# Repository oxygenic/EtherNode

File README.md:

# EtherNode
Slim STM32H7-based Ethernet device with several IOs and signal types which can be controlled via Telnet, supports MODBUS, REST and MQTT as well as small programs running from the device directly 

The EtherNode is an industrial IO-extender that comes with different types of input- and output-signals and a wide range of communication interfaces. Thus it can be used as remote Ethernet IO-module for different other scenarios and applications. Possible usage scenarios would be applications where the EtherNode acts as slim TCP module for a PLC and where it autonomously performs distributed and remote I/O operations that are triggered via simple and easy to use commands.

The EtherNode Compact IO module can be integrated into every machine network and provides the following features:
- wide-range power supply allows input voltages from 9V to 32V
- 8 galvanically insulated digital inputs which can be operated with external power in range 5..24V
- 2 of the digital inputs optionally can be used with a quadrature encoder for counting steps (position), speed and acceleration
- 8 galvanically insulated digital outputs which can be operated with external power in range 5..24V
- 2 of the digital outputs optionally can issue freely definable frequencies of up to 500 kHz with programmable pulse-width (PWM)
- 2 of the digital outputs optionally can be used to drive control two stepper motor axes with a step frequency of up to 100 kHz, acceleration ramps and referencing
- 2 high-impedance analogue inputs in range 0..10V with a resolution of 16 bits
- Ethernet interface to connect with host (control-PC / embedded device / PLC)
- control via Telnet ASCII commands, MODBUS, MQTT (plain and JSON) or HTTP REST API (plain and JSON)
- stand-alone operation: conditions and flows can be defined and stored on the device for autonomous operation wiht and without communication via the communication interfaces
- fully operational with any control device such as a PLC or even a plain PC or a Raspberry Pi
- board designed to fit into compact housing with DIN rail mounting clamp available at https://de.rs-online.com/web/p/din-schienen-gehause/1862290 and at https://de.rs-online.com/web/p/din-schienen-gehause/0336868

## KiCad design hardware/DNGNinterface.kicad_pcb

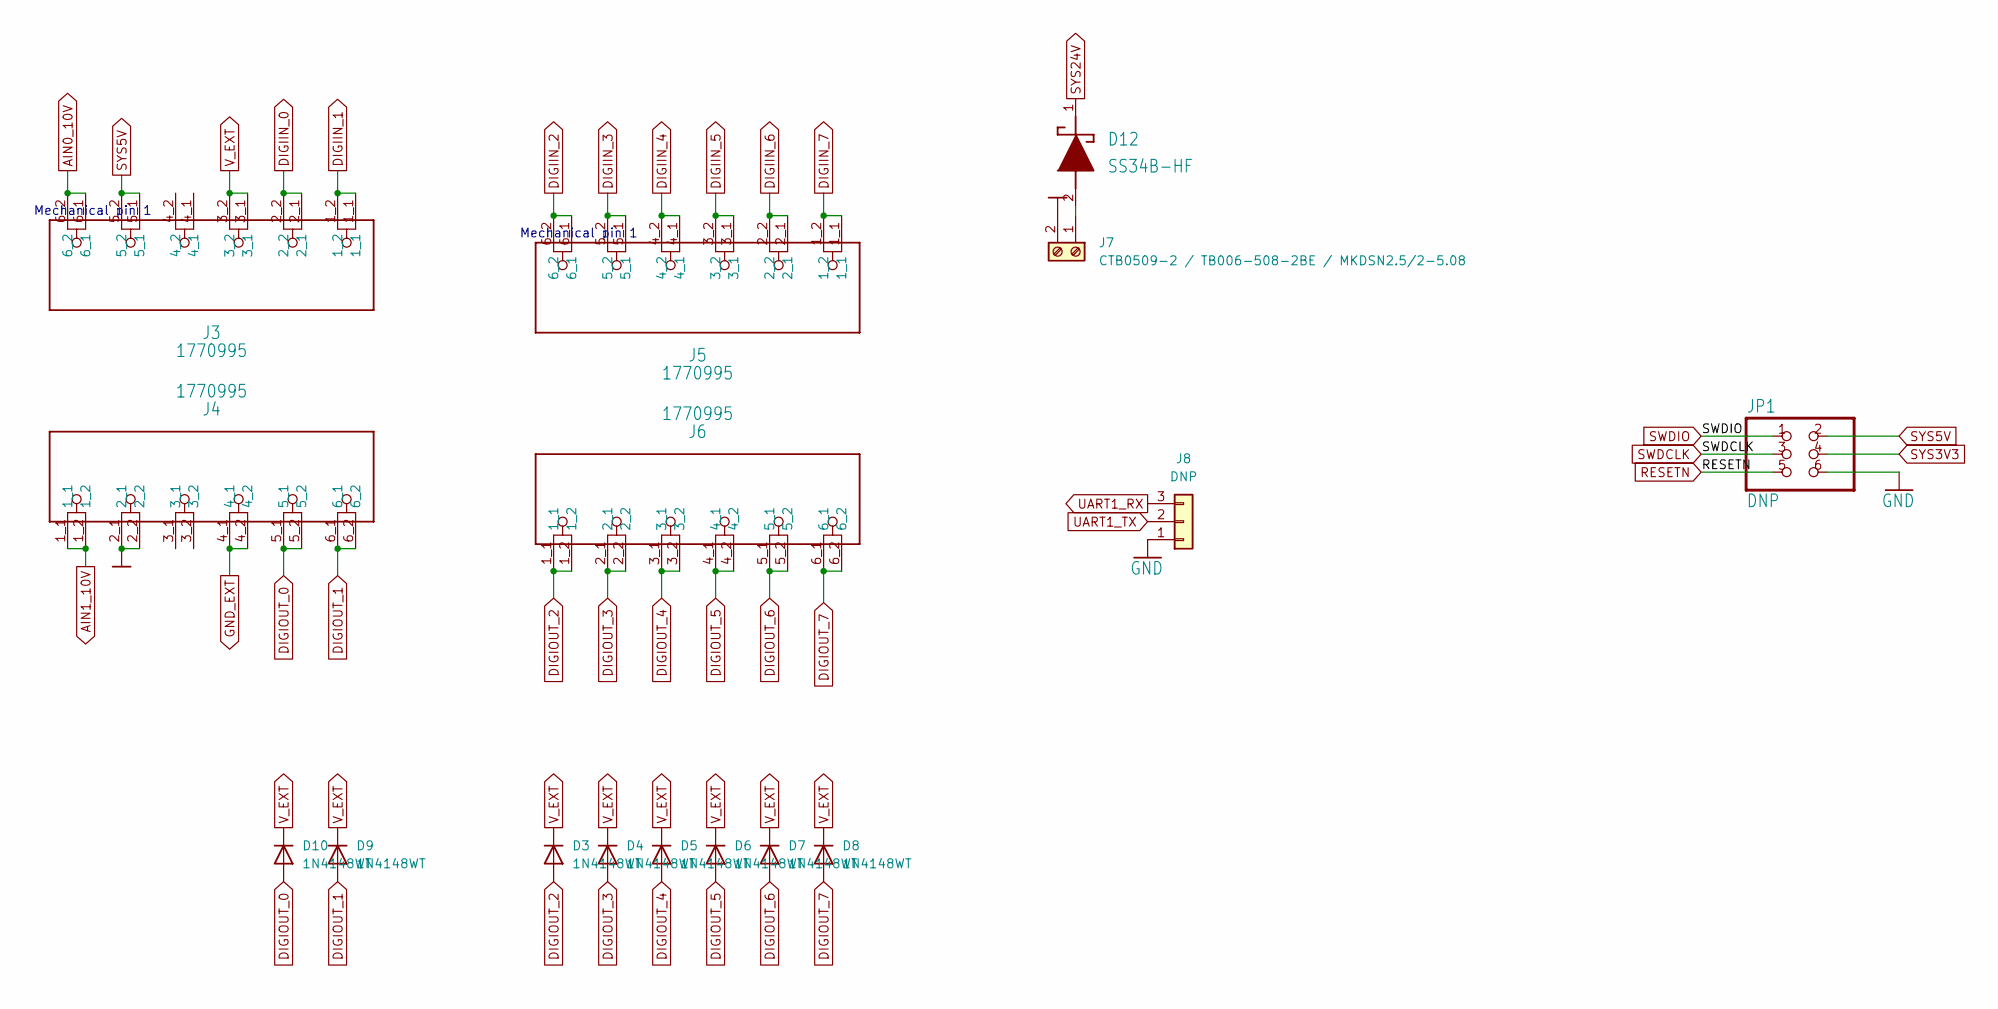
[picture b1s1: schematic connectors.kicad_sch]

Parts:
D3, D4, D5, D6, D7, D8, D9, D10: 1N4148WT; D_SOD-523
D12: SS34B-HF; SS34
J3, J4, J5, J6: 1770995; PHOENIX_1770995
J7: CTB0509-2 / TB006-508-2BE / MKDSN2.5/2-5.08; TerminalBlock_Phoenix_MKDS-1,5-2-5.08_1x02_P5.08mm_Horizont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
J8: DNP; PinHeader_1x03_P2.54mm_Vertical
JP1: DNP; PinHeader_2x03_P2.54mm_Vertical

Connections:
AIN0_10V: J3.6_1, J3.6_2; also elsewhere on the board
AIN1_10V: J4.1_1, J4.1_2; also elsewhere on the board
DIGIIN_0: J3.2_1, J3.2_2; also elsewhere on the board
DIGIIN_1: J3.1_1, J3.1_2; also elsewhere on the board
DIGIIN_2: J5.6_1, J5.6_2; also elsewhere on the board
DIGIIN_3: J5.5_1, J5.5_2; also elsewhere on the board
DIGIIN_4: J5.4_1, J5.4_2; also elsewhere on the board
DIGIIN_5: J5.3_1, J5.3_2; also elsewhere on the board
DIGIIN_6: J5.2_1, J5.2_2; also elsewhere on the board
DIGIIN_7: J5.1_1, J5.1_2; also elsewhere on the board
DIGIOUT_0: D10.2 (A), J4.5_1, J4.5_2; also elsewhere on the board
DIGIOUT_1: D9.2 (A), J4.6_1, J4.6_2; also elsewhere on the board
DIGIOUT_2: D3.2 (A), J6.1_1, J6.1_2; also elsewhere on the board
DIGIOUT_3: D4.2 (A), J6.2_1, J6.2_2; also elsewhere on the board
DIGIOUT_4: D5.2 (A), J6.3_1, J6.3_2; also elsewhere on the board
DIGIOUT_5: D6.2 (A), J6.4_1, J6.4_2; also elsewhere on the board
DIGIOUT_6: D7.2 (A), J6.5_1, J6.5_2; also elsewhere on the board
DIGIOUT_7: D8.2 (A), J6.6_1, J6.6_2; also elsewhere on the board
GND: J4.2_1, J4.2_2, J7.2, J8.1, JP1.6; also elsewhere on the board
GND_EXT: J4.4_1, J4.4_2; also elsewhere on the board
unnamed: D12.2 (A), J7.1
RESETN: JP1.5; also elsewhere on the board
SWDCLK: JP1.3; also elsewhere on the board
SWDIO: JP1.1; also elsewhere on the board
SYS3V3: JP1.4; also elsewhere on the board
SYS5V: J3.5_1, J3.5_2, JP1.2; also elsewhere on the board
SYS24V: D12.1 (K); also elsewhere on the board
UART1_RX: J8.3; also elsewhere on the board
UART1_TX: J8.2; also elsewhere on the board
V_EXT: D3.1 (K), D4.1 (K), D5.1 (K), D6.1 (K), D7.1 (K), D8.1 (K), D9.1 (K), D10.1 (K), J3.3_1, J3.3_2; also elsewhere on the board

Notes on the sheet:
Mechanical pin 1

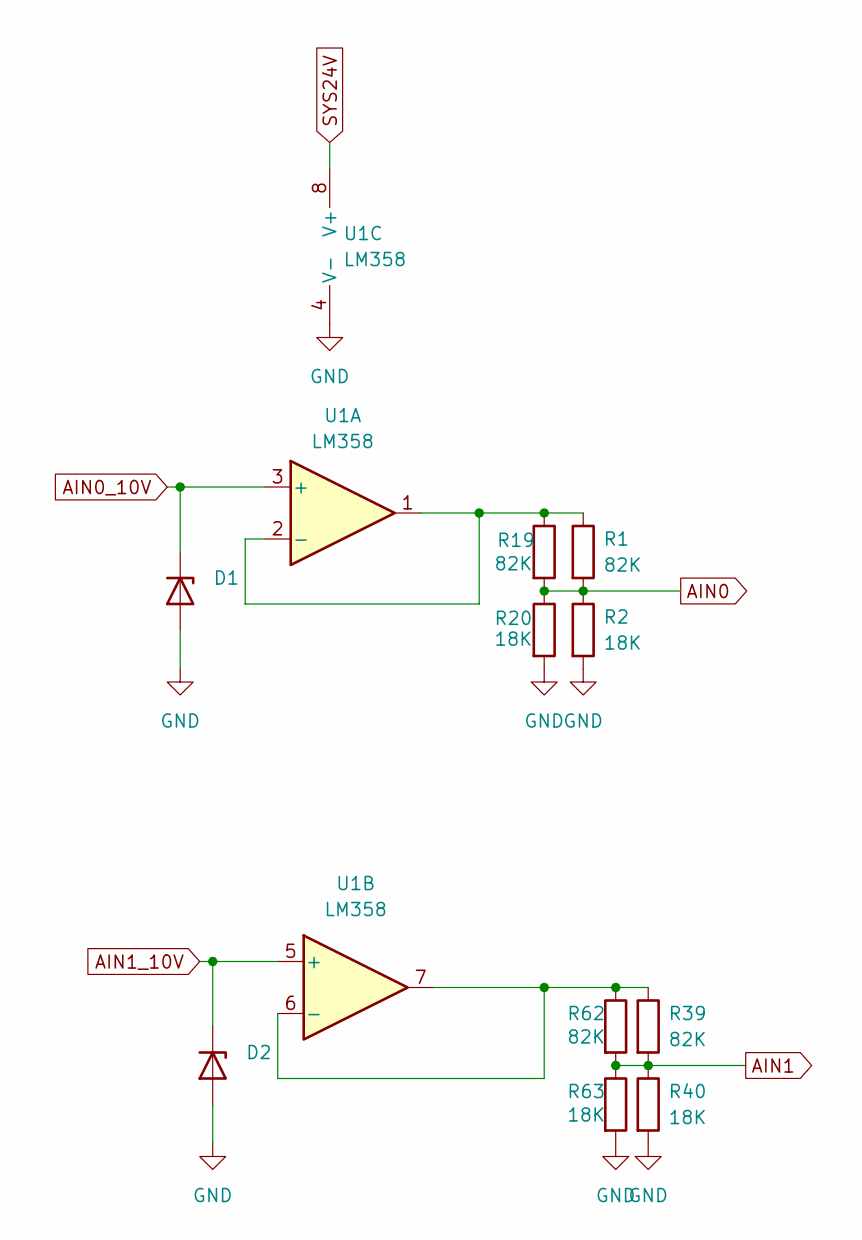
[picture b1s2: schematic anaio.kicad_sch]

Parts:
D1, D2: BZX84B10 / BZX84C10; SOT-23
R1, R19, R39, R62: 82K; R_0603_1608Metric
R2, R20, R40, R63: 18K; R_0603_1608Metric
U1: LM358; LM358DT

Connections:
AIN0: R1.2, R2.1, R19.2, R20.1; also elsewhere on the board
AIN0_10V: D1.3 (K), U1.3 (+); also elsewhere on the board
AIN1: R39.2, R40.1, R62.2, R63.1; also elsewhere on the board
AIN1_10V: D2.3 (K), U1.5 (+); also elsewhere on the board
GND: D1.1 (A), D2.1 (A), R2.2, R20.2, R40.2, R63.2, U1.4 (V-); also elsewhere on the board
unnamed: R1.1, R19.1, U1.1, U1.2 (-)
unnamed: R39.1, R62.1, U1.6 (-), U1.7
SYS24V: U1.8 (V+); also elsewhere on the board

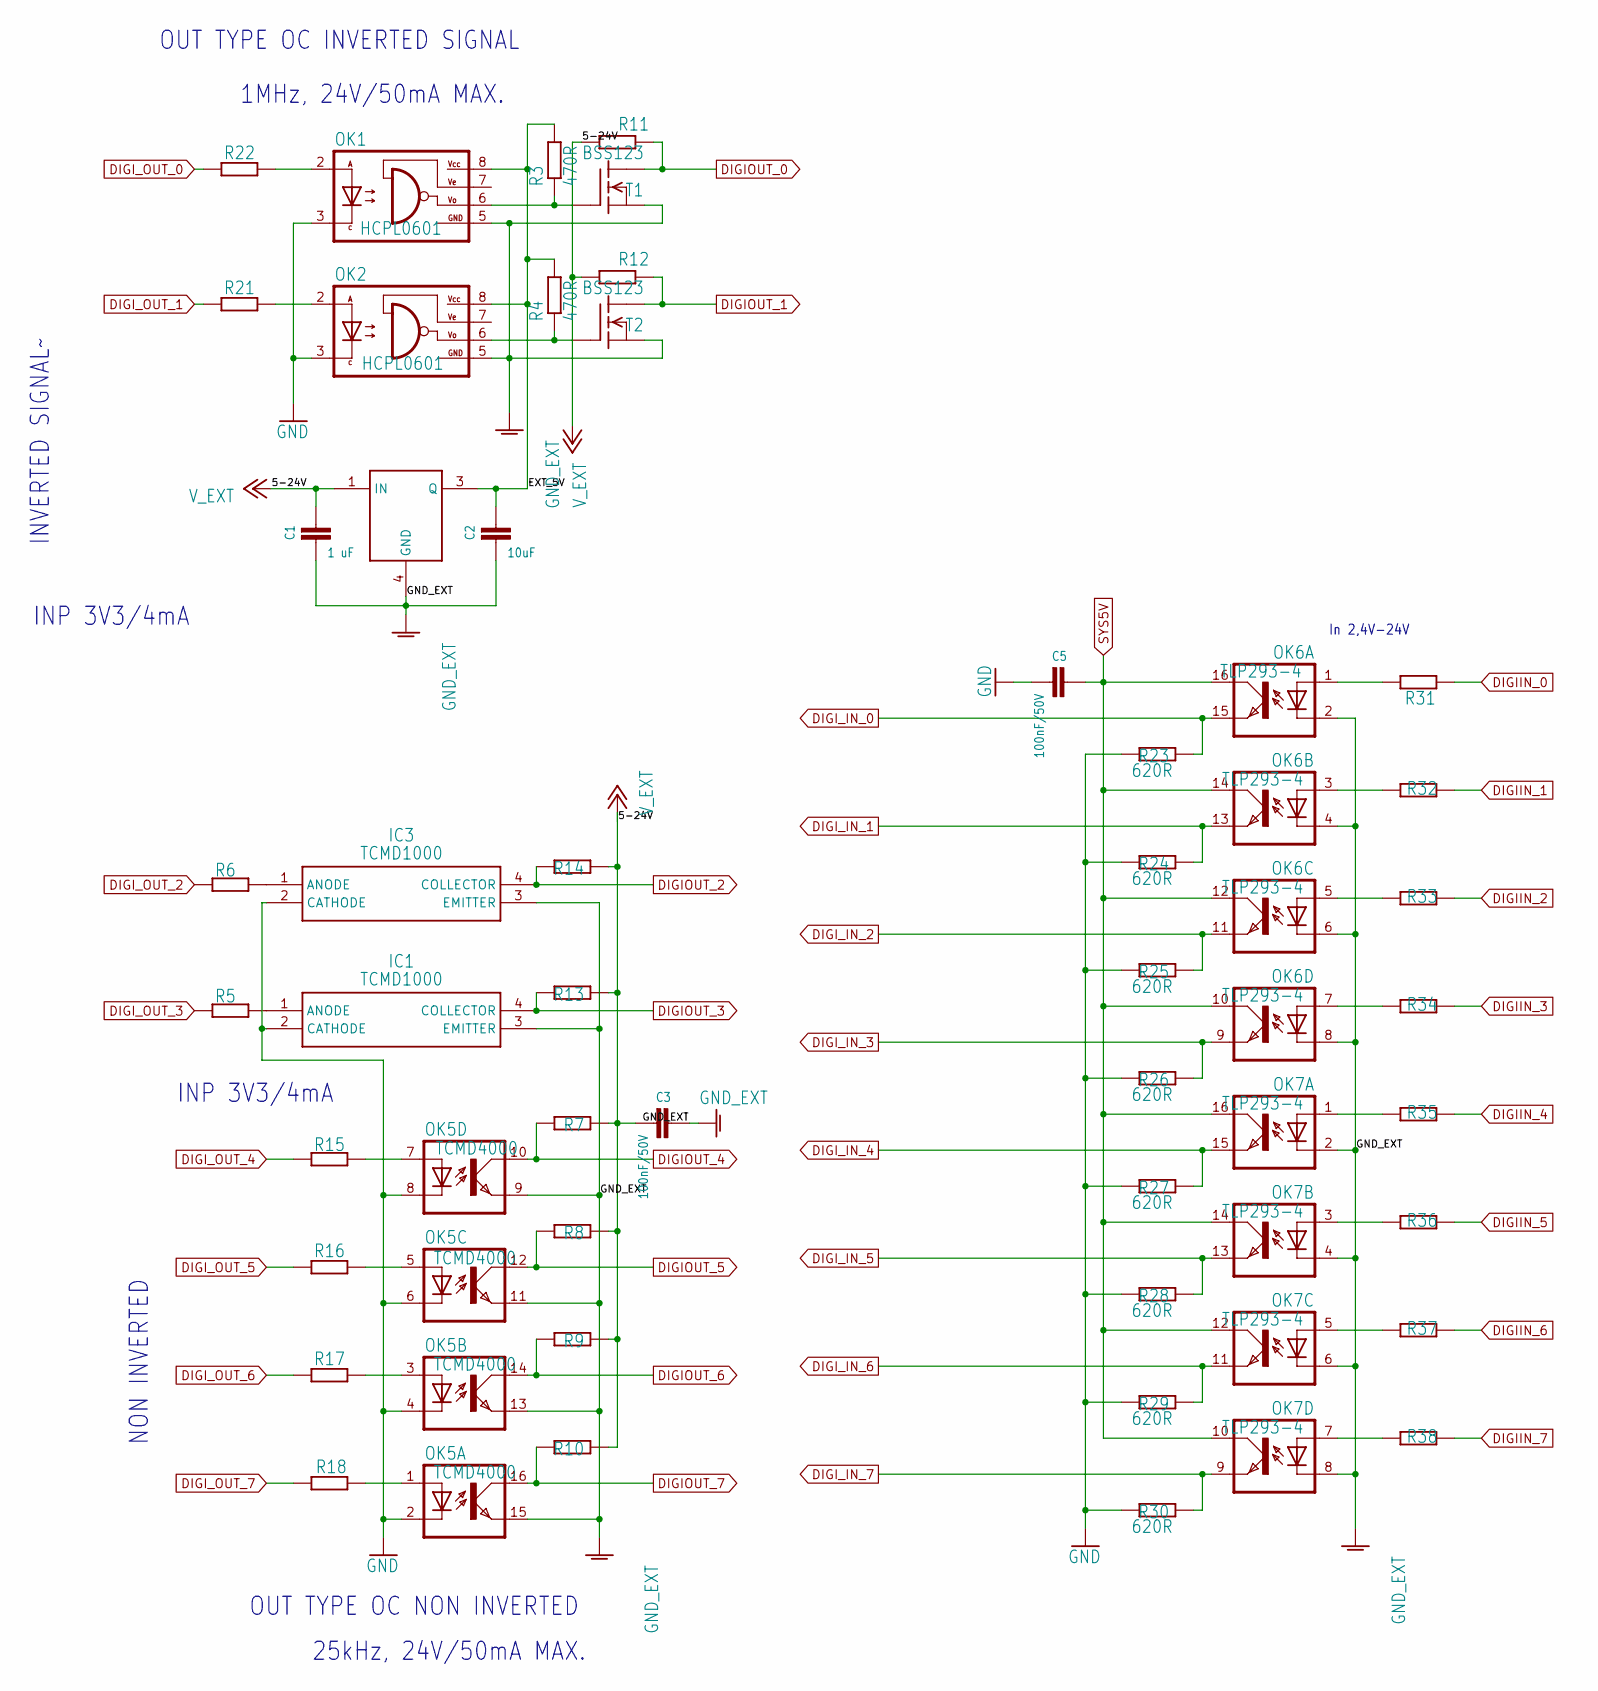
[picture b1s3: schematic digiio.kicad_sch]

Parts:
C1: 1 uF; C_0603_1608Metric
C2: 10uF; C_0603_1608Metric
C3, C5: 100nF/50V; C_0603_1608Metric
IC1, IC3: TCMD1000; SOIC127P695X210-4N
OK1, OK2: HCPL0601; HCLP0601
OK5: TCMD4000
OK6, OK7: TLP293-4; TLP293-4(E
R3, R4: 470R; R_0603_1608Metric
R5, R6, R15, R16, R17, R18, R21, R22: 270 R; R_0603_1608Metric
R7, R8, R9, R10, R11, R12, R13, R14: 2k2 0,75W ASC2010-2K2FT4 / RMCF2010JT2K20; R_2010_5025Metric
R23, R24, R25, R26, R27, R28, R29, R30: 620R; R_0603_1608Metric
R31, R32, R33, R34, R35, R36, R37, R38: 1k 0,75W RC2010JK-071KL / RMCF2010JT1K00 / CRMA20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; R_2010_5025Metric
T1, T2: BSS123
U$1: NCV4274CDT50RKG / NCV4274ADT50 / BD50FC0FP; NCV4274CDT50RKG

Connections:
/DigiIO/EXT_5V: C2.1, OK1.8 (VCC), OK2.8 (VCC), R3.2, R4.2, U$1.3 (Q)
DIGIIN_0: R31.2; also elsewhere on the board
DIGIIN_1: R32.2; also elsewhere on the board
DIGIIN_2: R33.2; also elsewhere on the board
DIGIIN_3: R34.2; also elsewhere on the board
DIGIIN_4: R35.2; also elsewhere on the board
DIGIIN_5: R36.2; also elsewhere on the board
DIGIIN_6: R37.2; also elsewhere on the board
DIGIIN_7: R38.2; also elsewhere on the board
DIGIOUT_0: R11.2, T1.3 (D1); also elsewhere on the board
DIGIOUT_1: R12.2, T2.3 (D1); also elsewhere on the board
DIGIOUT_2: IC3.4 (COLLECTOR), R14.2; also elsewhere on the board
DIGIOUT_3: IC1.4 (COLLECTOR), R13.2; also elsewhere on the board
DIGIOUT_4: OK5.10 (COL), R7.2; also elsewhere on the board
DIGIOUT_5: OK5.12 (COL), R8.2; also elsewhere on the board
DIGIOUT_6: OK5.14 (COL), R9.2; also elsewhere on the board
DIGIOUT_7: OK5.16 (COL), R10.2; also elsewhere on the board
DIGI_IN_0: OK6.15 (EMIT), R23.1; also elsewhere on the board
DIGI_IN_1: OK6.13 (EMIT), R24.1; also elsewhere on the board
DIGI_IN_2: OK6.11 (EMIT), R25.1; also elsewhere on the board
DIGI_IN_3: OK6.9 (EMIT), R26.1; also elsewhere on the board
DIGI_IN_4: OK7.15 (EMIT), R27.1; also elsewhere on the board
DIGI_IN_5: OK7.13 (EMIT), R28.1; also elsewhere on the board
DIGI_IN_6: OK7.11 (EMIT), R29.1; also elsewhere on the board
DIGI_IN_7: OK7.9 (EMIT), R30.1; also elsewhere on the board
DIGI_OUT_0: R22.1; also elsewhere on the board
DIGI_OUT_1: R21.1; also elsewhere on the board
DIGI_OUT_2: R6.1; also elsewhere on the board
DIGI_OUT_3: R5.1; also elsewhere on the board
DIGI_OUT_4: R15.1; also elsewhere on the board
DIGI_OUT_5: R16.1; also elsewhere on the board
DIGI_OUT_6: R17.1; also elsewhere on the board
DIGI_OUT_7: R18.1; also elsewhere on the board
GND: C5.2, IC1.2 (CATHODE), IC3.2 (CATHODE), OK1.3 (C), OK2.3 (C), OK5.2 (C), OK5.4 (C), OK5.6 (C), OK5.8 (C), R23.2, R24.2, R25.2, R26.2, R27.2, R28.2, R29.2, R30.2; also elsewhere on the board
GND_EXT: C1.2, C2.2, C3.1, IC1.3 (EMITTER), IC3.3 (EMITTER), OK1.5 (GND), OK2.5 (GND), OK5.9 (EMIT), OK5.11 (EMIT), OK5.13 (EMIT), OK5.15 (EMIT), OK6.2 (C), OK6.4 (C), OK6.6 (C), OK6.8 (C), OK7.2 (C), OK7.4 (C), OK7.6 (C), OK7.8 (C), T1.2 (S), T2.2 (S), U$1.4 (GND); also elsewhere on the board
unnamed: IC1.1 (ANODE), R5.2
unnamed: IC3.1 (ANODE), R6.2
unnamed: OK1.2 (A), R22.2
unnamed: OK1.6 (VO), R3.1, T1.1 (G)
unnamed: OK2.2 (A), R21.2
unnamed: OK2.6 (VO), R4.1, T2.1 (G)
unnamed: OK5.1 (A), R18.2
unnamed: OK5.3 (A), R17.2
unnamed: OK5.5 (A), R16.2
unnamed: OK5.7 (A), R15.2
unnamed: OK6.1 (A), R31.1
unnamed: OK6.3 (A), R32.1
unnamed: OK6.5 (A), R33.1
unnamed: OK6.7 (A), R34.1
unnamed: OK7.1 (A), R35.1
unnamed: OK7.3 (A), R36.1
unnamed: OK7.5 (A), R37.1
unnamed: OK7.7 (A), R38.1
SYS5V: C5.1, OK6.10 (COL), OK6.12 (COL), OK6.14 (COL), OK6.16 (COL), OK7.10 (COL), OK7.12 (COL), OK7.14 (COL), OK7.16 (COL); also elsewhere on the board
V_EXT: C1.1, C3.2, R7.1, R8.1, R9.1, R10.1, R11.1, R12.1, R13.1, R14.1, U$1.1 (IN); also elsewhere on the board

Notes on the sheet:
OUT TYPE OC NON INVERTED
NON INVERTED
INP 3V3/4mA
OUT TYPE OC INVERTED SIGNAL
25kHz, 24V/50mA MAX.
In 2,4V-24V
1MHz, 24V/50mA MAX.
INVERTED SIGNAL~~{}

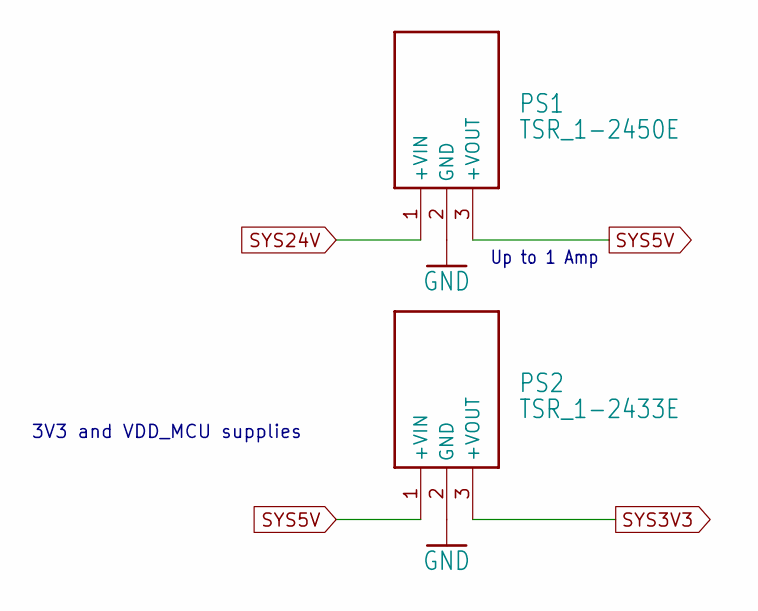
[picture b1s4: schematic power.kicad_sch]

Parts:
PS1: TSR_1-2450E; Converter_DCDC_TRACO_TSR1-xxxxE_THT
PS2: TSR_1-2433E; Converter_DCDC_TRACO_TSR1-xxxxE_THT

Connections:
GND: PS1.2 (GND), PS2.2 (GND); also elsewhere on the board
SYS3V3: PS2.3 (+VOUT); also elsewhere on the board
SYS5V: PS1.3 (+VOUT), PS2.1 (+VIN); also elsewhere on the board
SYS24V: PS1.1 (+VIN); also elsewhere on the board

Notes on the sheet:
Up to 1 Amp
3V3 and VDD_MCU supplies

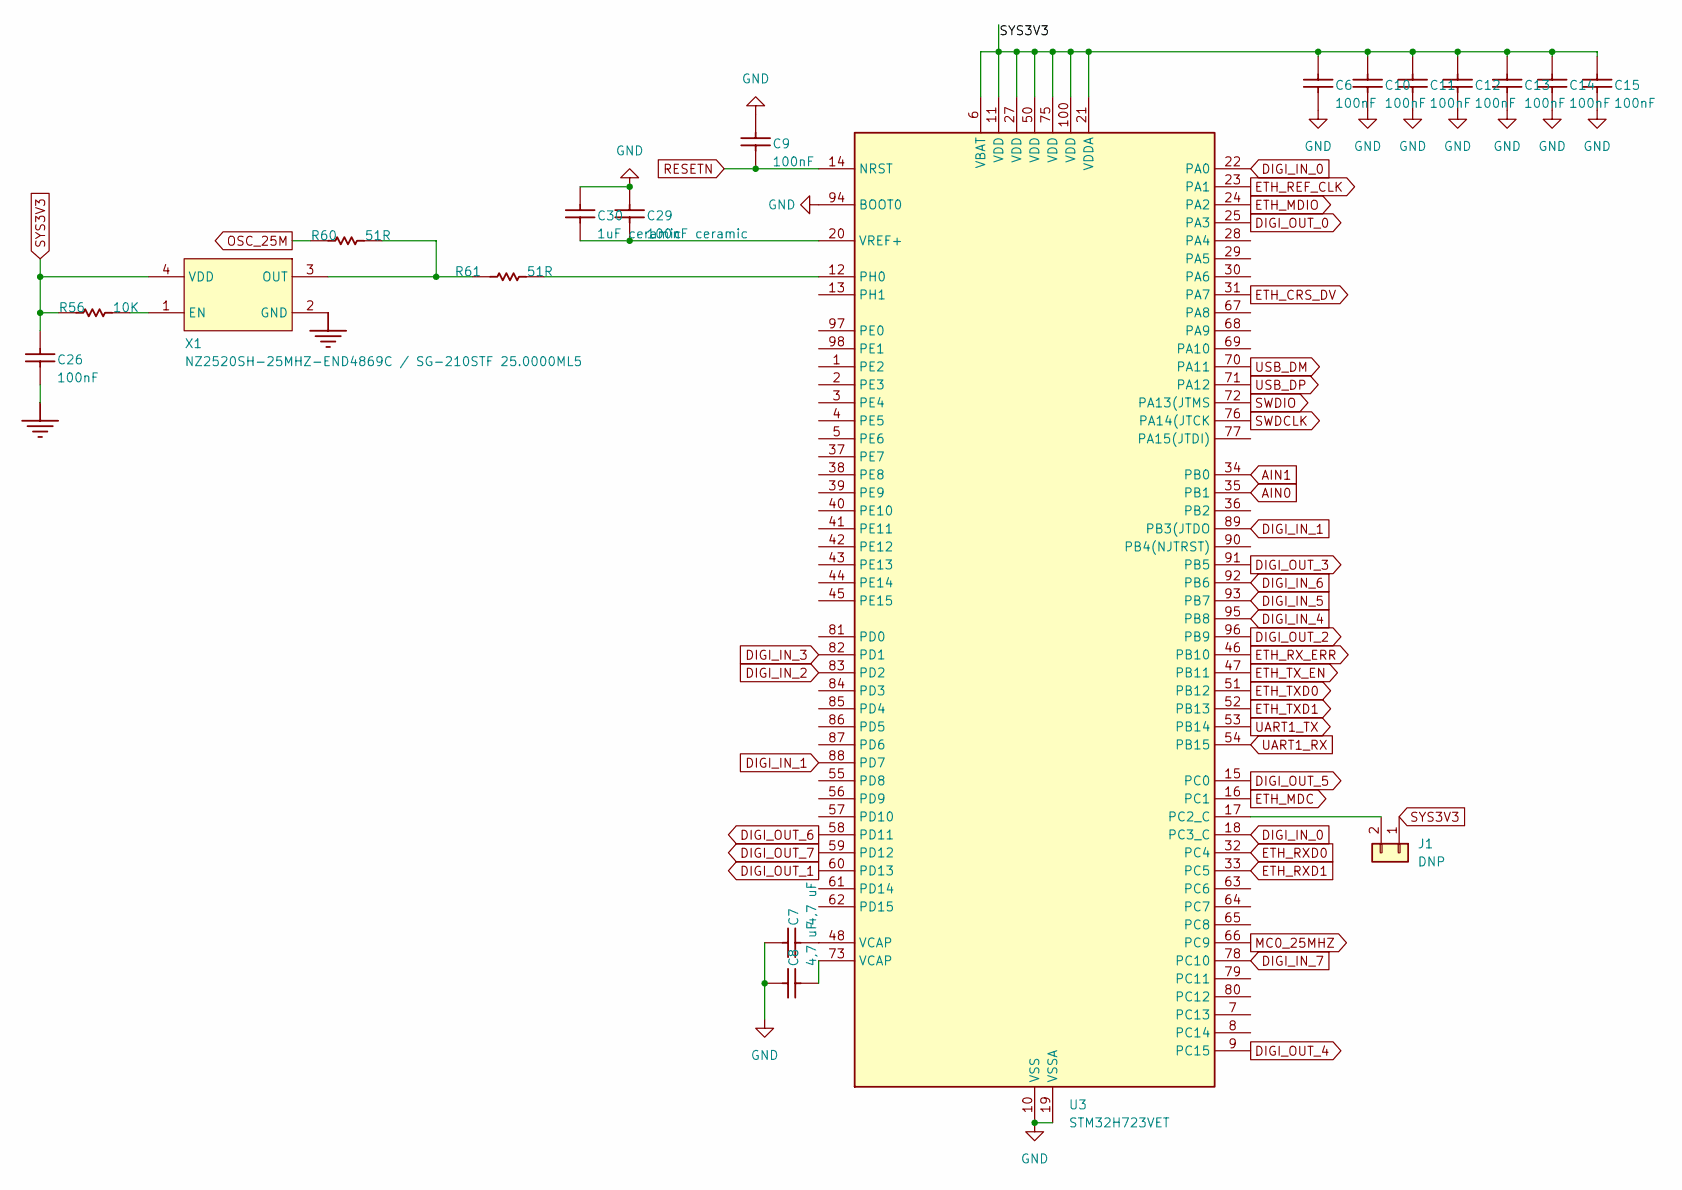
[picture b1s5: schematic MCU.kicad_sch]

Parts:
C6, C9, C10, C11, C12, C13, C14, C15, C26: 100nF; C_0603_1608Metric; PART_TYPE Capacitor
C7, C8: 4,7 uF; C_0603_1608Metric; PART_TYPE Capacitor
C29: 100nF ceramic; C_0603_1608Metric; PART_TYPE Capacitor
C30: 1uF ceramic; C_0603_1608Metric; PART_TYPE Capacitor
J1: DNP; PinHeader_1x02_P1.00mm_Vertical
R56: 10K; R_0603_1608Metric; PART_TYPE Resistor
R60, R61: 51R; R_0603_1608Metric; PART_TYPE Resistor
U3: STM32H723VET; LQFP-100_14x14mm_P0.5mm
X1: NZ2520SH-25MHZ-END4869C / SG-210STF 25.0000ML5; SG210STF250000ML5; PART_TYPE Crystal_Osc

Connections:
AIN0: U3.35 (PB1); also elsewhere on the board
AIN1: U3.34 (PB0); also elsewhere on the board
DIGI_IN_0: U3.18 (PC3_C), U3.22 (PA0); also elsewhere on the board
DIGI_IN_1: U3.88 (PD7), U3.89 (PB3(JTDO); also elsewhere on the board
DIGI_IN_2: U3.83 (PD2); also elsewhere on the board
DIGI_IN_3: U3.82 (PD1); also elsewhere on the board
DIGI_IN_4: U3.95 (PB8); also elsewhere on the board
DIGI_IN_5: U3.93 (PB7); also elsewhere on the board
DIGI_IN_6: U3.92 (PB6); also elsewhere on the board
DIGI_IN_7: U3.78 (PC10); also elsewhere on the board
DIGI_OUT_0: U3.25 (PA3); also elsewhere on the board
DIGI_OUT_1: U3.60 (PD13); also elsewhere on the board
DIGI_OUT_2: U3.96 (PB9); also elsewhere on the board
DIGI_OUT_3: U3.91 (PB5); also elsewhere on the board
DIGI_OUT_4: U3.9 (PC15); also elsewhere on the board
DIGI_OUT_5: U3.15 (PC0); also elsewhere on the board
DIGI_OUT_6: U3.58 (PD11); also elsewhere on the board
DIGI_OUT_7: U3.59 (PD12); also elsewhere on the board
ETH_CRS_DV: U3.31 (PA7); also elsewhere on the board
ETH_MDC: U3.16 (PC1); also elsewhere on the board
ETH_MDIO: U3.24 (PA2); also elsewhere on the board
ETH_REF_CLK: U3.23 (PA1); also elsewhere on the board
ETH_RXD0: U3.32 (PC4); also elsewhere on the board
ETH_RXD1: U3.33 (PC5); also elsewhere on the board
ETH_RX_ERR: U3.46 (PB10); also elsewhere on the board
ETH_TXD0: U3.51 (PB12); also elsewhere on the board
ETH_TXD1: U3.52 (PB13); also elsewhere on the board
ETH_TX_EN: U3.47 (PB11); also elsewhere on the board
GND: C6.1, C7.2, C8.2, C9.2, C10.1, C11.1, C12.1, C13.1, C14.1, C15.1, C26.1, C29.2, C30.2, U3.10 (VSS), U3.19 (VSSA), U3.26 (VSS), U3.49 (VSS), U3.74 (VSS), U3.94 (BOOT0), U3.99 (VSS), X1.2 (GND); also elsewhere on the board
MC0_25MHZ: U3.66 (PC9)
unnamed: C7.1, U3.48 (VCAP)
unnamed: C8.1, U3.73 (VCAP)
unnamed: J1.2, U3.17 (PC2_C)
unnamed: R61.2, U3.12 (PH0)
unnamed: C29.1, C30.1, U3.20 (VREF+)
unnamed: R56.1, X1.1 (EN)
unnamed: R60.2, R61.1, X1.3 (OUT)
OSC_25M: R60.1; also elsewhere on the board
RESETN: C9.1, U3.14 (NRST); also elsewhere on the board
SWDCLK: U3.76 (PA14(JTCK); also elsewhere on the board
SWDIO: U3.72 (PA13(JTMS); also elsewhere on the board
SYS3V3: C6.2, C10.2, C11.2, C12.2, C13.2, C14.2, C15.2, C26.2, J1.1, R56.2, U3.6 (VBAT), U3.11 (VDD), U3.21 (VDDA), U3.27 (VDD), U3.50 (VDD), U3.75 (VDD), U3.100 (VDD), X1.4 (VDD); also elsewhere on the board
UART1_RX: U3.54 (PB15); also elsewhere on the board
UART1_TX: U3.53 (PB14); also elsewhere on the board
USB_DM: U3.70 (PA11)
USB_DP: U3.71 (PA12)

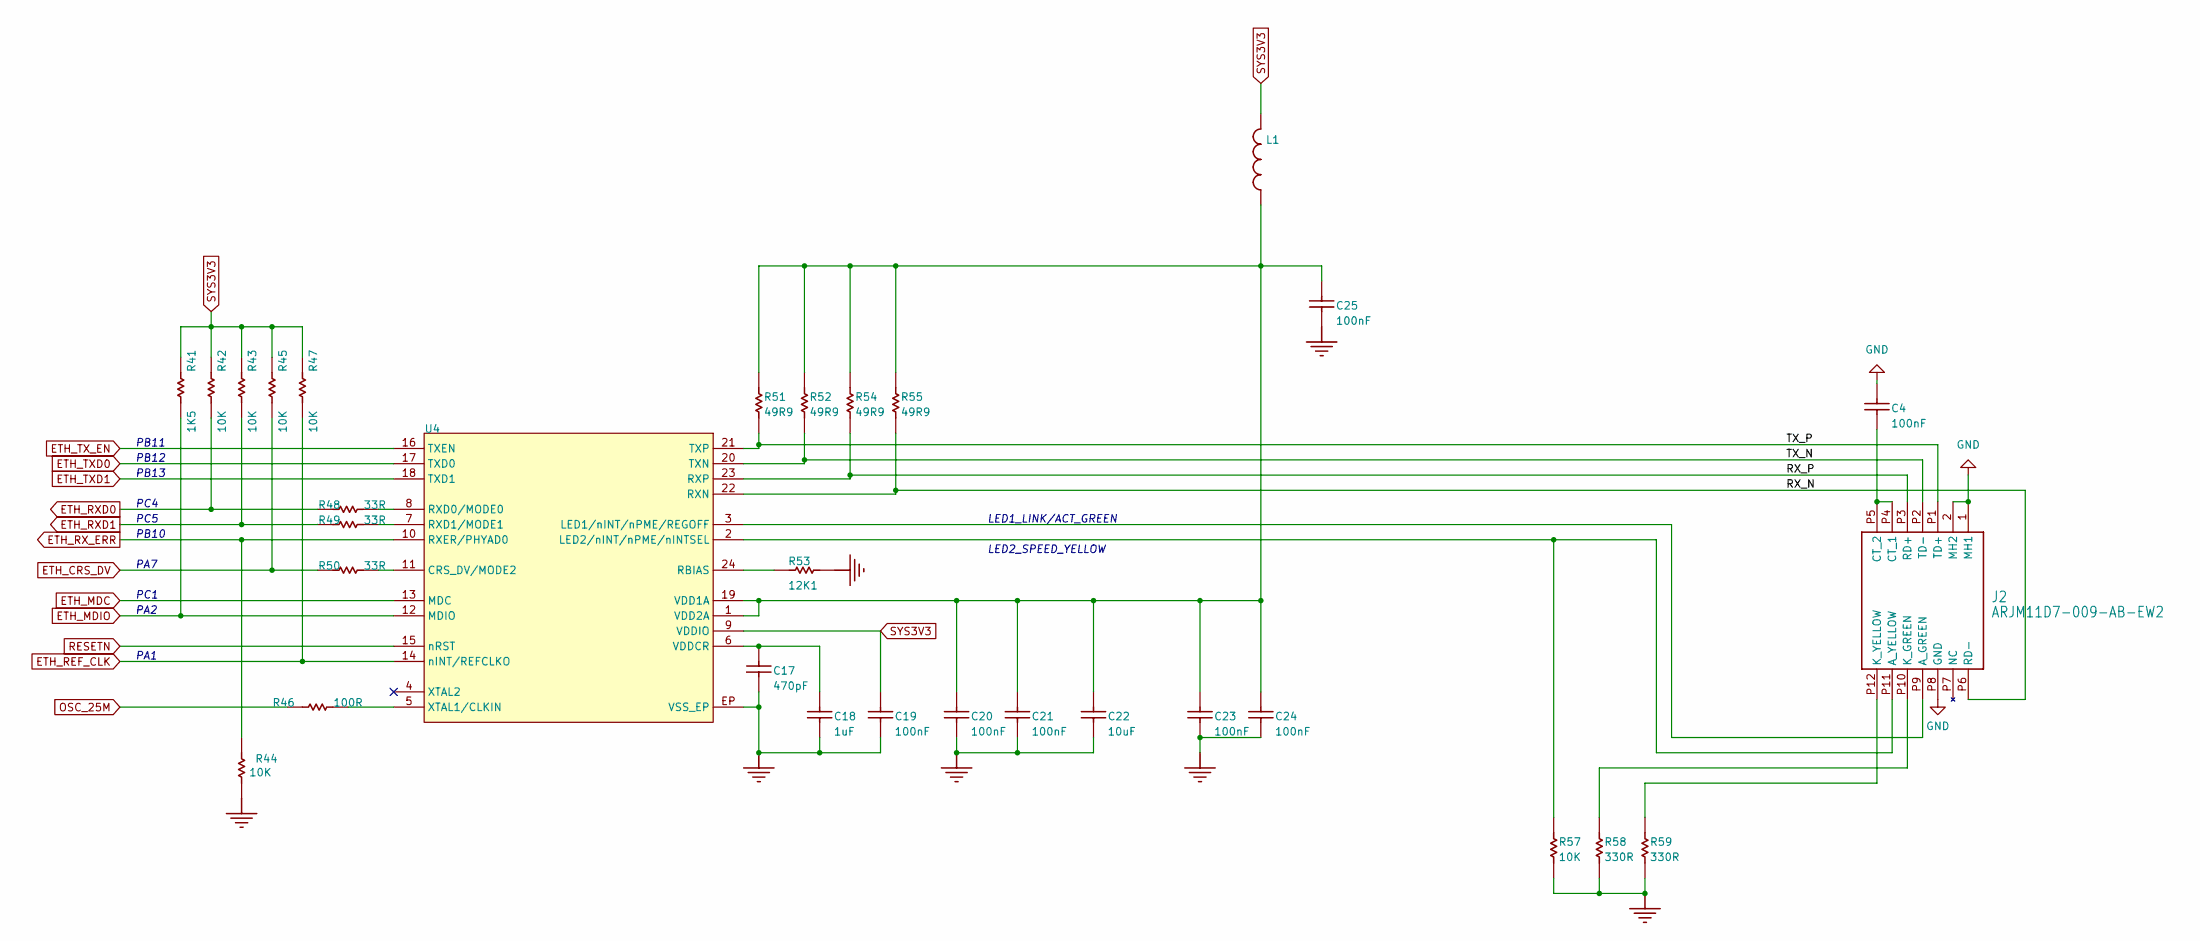
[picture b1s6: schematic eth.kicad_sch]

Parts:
C4: 100nF; C_0603_1608Metric; PART_TYPE Capacitor
C17: 470pF; C_0402_1005Metric; PART_TYPE Capacitor
C18: 1uF; C_0402_1005Metric; PART_TYPE Capacitor
C19, C20, C21, C23, C24, C25: 100nF; C_0402_1005Metric; PART_TYPE Capacitor
C22: 10uF; C_0402_1005Metric; PART_TYPE Capacitor
J2: ARJM11D7-009-AB-EW2; ARJM11D7009ABEW2
L1: FCM1608KF-601T03; L_0603_1608Metric; PART_TYPE Inductor
R41: 1K5; R_0402_1005Metric; PART_TYPE Resistor
R42, R43, R44, R45, R47, R57: 10K; R_0402_1005Metric; PART_TYPE Resistor
R46: 100R; R_0402_1005Metric; PART_TYPE Resistor
R48, R49, R50: 33R; R_0402_1005Metric; PART_TYPE Resistor
R51, R52, R54, R55: 49R9; R_0603_1608Metric; PART_TYPE Resistor
R53: 12K1; R_0402_1005Metric; PART_TYPE Resistor
R58, R59: 330R; R_0402_1005Metric; PART_TYPE Resistor
U4: LAN8742A-CZ-TR; LAN8742A; PART_TYPE IC

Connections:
/ETH/RX_N: J2.P6 (RD-), R55.1, U4.22 (RXN)
/ETH/RX_P: J2.P3 (RD+), R54.1, U4.23 (RXP)
/ETH/TX_N: J2.P2 (TD-), R52.1, U4.20 (TXN)
/ETH/TX_P: J2.P1 (TD+), R51.1, U4.21 (TXP)
ETH_CRS_DV: R45.2, R50.1; also elsewhere on the board
ETH_MDC: U4.13 (MDC); also elsewhere on the board
ETH_MDIO: R41.1, U4.12 (MDIO); also elsewhere on the board
ETH_REF_CLK: R47.2, U4.14 (nINT/REFCLKO); also elsewhere on the board
ETH_RXD0: R42.1, R48.1; also elsewhere on the board
ETH_RXD1: R43.1, R49.1; also elsewhere on the board
ETH_RX_ERR: R44.1, U4.10 (RXER/PHYAD0); also elsewhere on the board
ETH_TXD0: U4.17 (TXD0); also elsewhere on the board
ETH_TXD1: U4.18 (TXD1); also elsewhere on the board
ETH_TX_EN: U4.16 (TXEN); also elsewhere on the board
GND: C4.1, C17.1, C18.1, C19.2, C20.2, C21.2, C22.1, C23.2, C24.2, C25.1, J2.1 (MH1), J2.2 (MH2), J2.P8 (GND), R44.2, R53.2, R57.1, R58.1, R59.1, U4.EP (VSS_EP); also elsewhere on the board
unnamed: J2.P9 (A_GREEN), U4.3 (LED1/nINT/nPME/REGOFF)
unnamed: J2.P11 (A_YELLOW), R57.2, U4.2 (LED2/nINT/nPME/nINTSEL)
unnamed: C4.2, J2.P4 (CT_1), J2.P5 (CT_2)
unnamed: J2.P10 (K_GREEN), R58.2
unnamed: J2.P12 (K_YELLOW), R59.2
unnamed: R50.2, U4.11 (CRS_DV/MODE2)
unnamed: R53.1, U4.24 (RBIAS)
unnamed: R48.2, U4.8 (RXD0/MODE0)
unnamed: R49.2, U4.7 (RXD1/MODE1)
unnamed: C20.1, C21.1, C22.2, C23.1, C24.1, C25.2, L1.1, R51.2, R52.2, R54.2, R55.2, U4.1 (VDD2A), U4.19 (VDD1A)
unnamed: C17.2, C18.2, U4.6 (VDDCR)
unnamed: R46.2, U4.5 (XTAL1/CLKIN)
OSC_25M: R46.1; also elsewhere on the board
RESETN: U4.15 (nRST); also elsewhere on the board
SYS3V3: C19.1, L1.2, R41.2, R42.2, R43.2, R45.1, R47.1, U4.9 (VDDIO); also elsewhere on the board

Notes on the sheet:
PB13
LED2_SPEED_YELLOW
PC5
PC1
PB10
PA2
PA7
PB11
LED1_LINK/ACT_GREEN
PC4
PB12
PA1

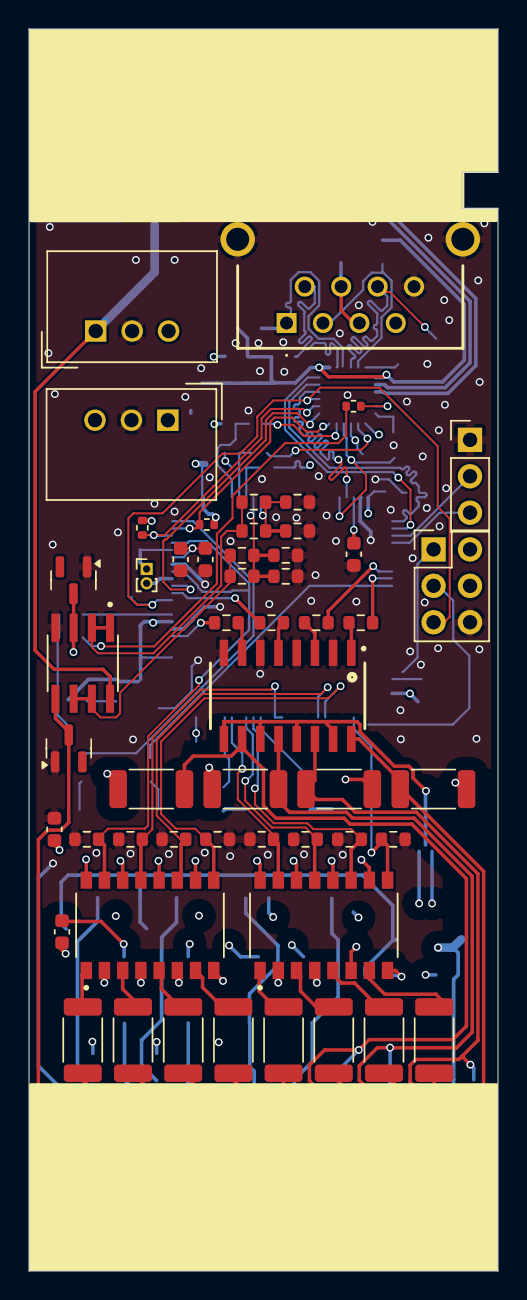
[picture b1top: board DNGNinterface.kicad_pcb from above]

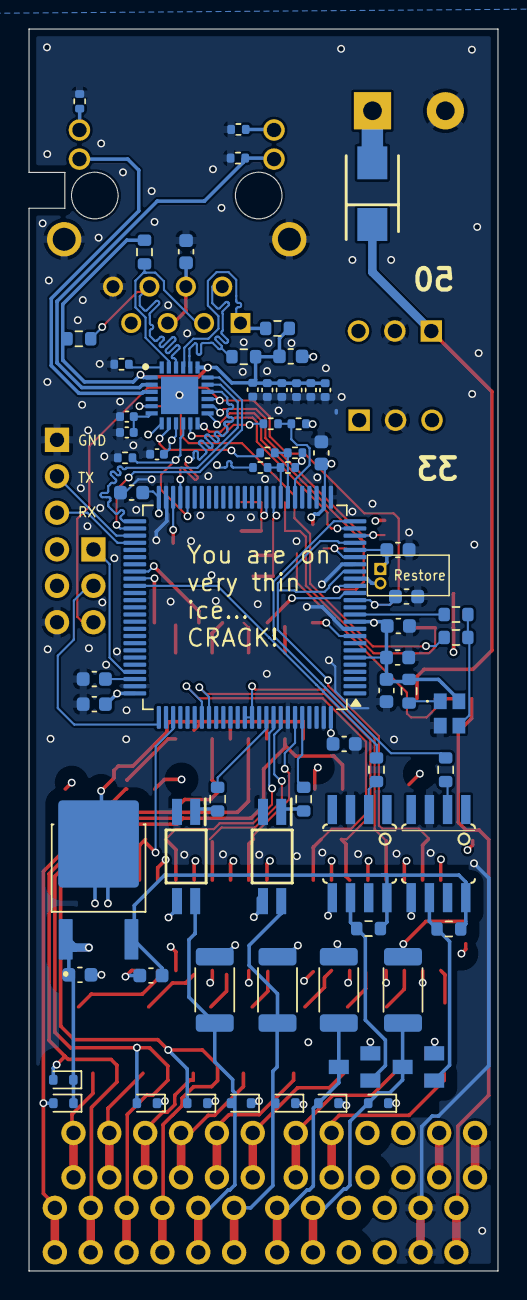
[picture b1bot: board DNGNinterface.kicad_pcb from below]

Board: 4 copper layers, 32.7 x 86.6 mm, 127 parts (70 on the bottom side), 103 nets.

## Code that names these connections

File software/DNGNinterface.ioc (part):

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Mcu.Name=STM32H723VETx
Mcu.Package=LQFP100
Mcu.UserName=STM32H723VETx
PA0.GPIOParameters=GPIO_PuPd
PA0.GPIO_PuPd=GPIO_PULLDOWN
PA0.Signal=S_TIM2_CH1_ETR
PA1.GPIOParameters=GPIO_Speed
PA1.GPIO_Speed=GPIO_SPEED_FREQ_VERY_HIGH
PA1.Mode=RMII
PA1.Signal=ETH_REF_CLK
PA13(JTMS/SWDIO).Mode=Serial_Wire
PA13(JTMS/SWDIO).Signal=DEBUG_JTMS-SWDIO
PA14(JTCK/SWCLK).Mode=Serial_Wire
PA14(JTCK/SWCLK).Signal=DEBUG_JTCK-SWCLK
PA2.GPIOParameters=GPIO_Speed
PA2.GPIO_Speed=GPIO_SPEED_FREQ_VERY_HIGH
PA2.Mode=RMII
PA2.Signal=ETH_MDIO
PA3.GPIOParameters=PinState,GPIO_PuPd,GPIO_Label
PA3.GPIO_Label=DIGI_OUT_0
PA3.GPIO_PuPd=GPIO_PULLDOWN
PA3.PinState=GPIO_PIN_SET
PA3.Signal=GPIO_Output
PA7.GPIOParameters=GPIO_Speed
PA7.GPIO_Speed=GPIO_SPEED_FREQ_VERY_HIGH
PA7.Mode=RMII
PA7.Signal=ETH_CRS_DV
PB0.GPIOParameters=GPIO_Label
PB0.GPIO_Label=AIN1
PB0.Signal=ADCx_INP9
PB1.GPIOParameters=GPIO_Label
PB1.GPIO_Label=AIN0
PB1.Signal=ADCx_INP5
PB10.Signal=ETH_RX_ER
PB11.GPIOParameters=GPIO_Speed
PB11.GPIO_Speed=GPIO_SPEED_FREQ_VERY_HIGH
PB11.Mode=RMII
PB11.Signal=ETH_TX_EN
PB12.GPIOParameters=GPIO_Speed
PB12.GPIO_Speed=GPIO_SPEED_FREQ_VERY_HIGH
PB12.Mode=RMII
PB12.Signal=ETH_TXD0
PB13.GPIOParameters=GPIO_Speed
PB13.GPIO_Speed=GPIO_SPEED_FREQ_VERY_HIGH
PB13.Mode=RMII
PB13.Signal=ETH_TXD1
PB14.Mode=Asynchronous
PB14.Signal=USART1_TX
PB15.Mode=Asynchronous
PB15.Signal=USART1_RX
PB3(JTDO/TRACESWO).GPIOParameters=GPIO_PuPd
PB3(JTDO/TRACESWO).GPIO_PuPd=GPIO_PULLDOWN
PB3(JTDO/TRACESWO).Signal=S_TIM2_CH2
PB5.GPIOParameters=GPIO_PuPd,GPIO_Label
PB5.GPIO_Label=DIGI_OUT_3
PB5.GPIO_PuPd=GPIO_PULLDOWN
PB5.Signal=GPIO_Output
PB6.GPIOParameters=GPIO_PuPd,GPIO_Label
PB6.GPIO_Label=DIGI_IN_6
PB6.GPIO_PuPd=GPIO_PULLDOWN
PB6.Signal=GPIO_Input
PB7.GPIOParameters=GPIO_PuPd,GPIO_Label
PB7.GPIO_Label=DIGI_IN_5
PB7.GPIO_PuPd=GPIO_PULLDOWN
PB7.Signal=GPIO_Input
PB8.GPIOParameters=GPIO_PuPd,GPIO_Label
PB8.GPIO_Label=DIGI_IN_4
PB8.GPIO_PuPd=GPIO_PULLDOWN
PB8.Signal=GPIO_Input
PB9.GPIOParameters=GPIO_PuPd,GPIO_Label
PB9.GPIO_Label=DIGI_OUT_2
PB9.GPIO_PuPd=GPIO_PULLDOWN
PB9.Signal=GPIO_Output
PC0.GPIOParameters=GPIO_PuPd,GPIO_Label
PC0.GPIO_Label=DIGI_OUT_5
PC0.GPIO_PuPd=GPIO_PULLDOWN
PC0.Signal=GPIO_Output
PC1.GPIOParameters=GPIO_Speed
PC1.GPIO_Speed=GPIO_SPEED_FREQ_VERY_HIGH
PC1.Mode=RMII
PC1.Signal=ETH_MDC
PC10.GPIOParameters=GPIO_PuPd,GPIO_Label
PC10.GPIO_Label=DIGI_IN_7
PC10.GPIO_PuPd=GPIO_PULLDOWN
PC10.Signal=GPIO_Input
PC15-OSC32_OUT.GPIOParameters=GPIO_PuPd,GPIO_Label,GPIO_ModeDefaultOutputPP
PC15-OSC32_OUT.GPIO_Label=DIGI_OUT_4
PC15-OSC32_OUT.GPIO_ModeDefaultOutputPP=GPIO_MODE_OUTPUT_PP
PC15-OSC32_OUT.GPIO_PuPd=GPIO_PULLDOWN
PC15-OSC32_OUT.Signal=GPIO_Output
PC2_C.GPIOParameters=GPIO_PuPd,GPIO_Label
PC2_C.GPIO_Label=SET_DEFAULT
PC2_C.GPIO_PuPd=GPIO_PULLDOWN
PC2_C.Signal=GPIO_Input
PC3_C.GPIOParameters=GPIO_PuPd,GPIO_Label
PC3_C.GPIO_Label=DIGI_IN_0
PC3_C.GPIO_PuPd=GPIO_PULLDOWN
PC3_C.Signal=GPIO_Input
PC4.GPIOParameters=GPIO_Speed
PC4.GPIO_Speed=GPIO_SPEED_FREQ_VERY_HIGH
PC4.Mode=RMII
PC4.Signal=ETH_RXD0
PC5.GPIOParameters=GPIO_Speed
PC5.GPIO_Speed=GPIO_SPEED_FREQ_VERY_HIGH
PC5.Mode=RMII
PC5.Signal=ETH_RXD1
PC9.Mode=Clock-out-2
PC9.Signal=RCC_MCO_2
PD1.GPIOParameters=GPIO_PuPd,GPIO_Label
PD1.GPIO_Label=DIGI_IN_3
PD1.GPIO_PuPd=GPIO_PULLDOWN
PD1.Signal=GPIO_Input
PD11.GPIOParameters=PinState,GPIO_PuPd,GPIO_Label
PD11.GPIO_Label=DIGI_OUT_6
PD11.GPIO_PuPd=GPIO_PULLDOWN
PD11.PinState=GPIO_PIN_RESET
PD11.Signal=GPIO_Output
PD12.GPIOParameters=GPIO_PuPd,GPIO_Label
PD12.GPIO_Label=DIGI_OUT_7
PD12.GPIO_PuPd=GPIO_PULLDOWN
PD12.Signal=GPIO_Output
PD13.GPIOParameters=PinState,GPIO_PuPd,GPIO_Label
PD13.GPIO_Label=DIGI_OUT_1
PD13.GPIO_PuPd=GPIO_PULLDOWN
PD13.PinState=GPIO_PIN_SET
PD13.Signal=GPIO_Output
PD2.GPIOParameters=GPIO_PuPd,GPIO_Label
PD2.GPIO_Label=DIGI_IN_2
PD2.GPIO_PuPd=GPIO_PULLDOWN
PD2.Signal=GPIO_Input
PD3.GPIOParameters=GPIO_PuPd,GPIO_Label
PD3.GPIO_Label=DIGI_IN_1OLD
PD3.GPIO_PuPd=GPIO_PULLDOWN
PD3.Signal=GPIO_Input
PD4.GPIOParameters=GPIO_PuPd,GPIO_Label
PD4.GPIO_Label=DIGI_IN_0OLD
PD4.GPIO_PuPd=GPIO_PULLDOWN
PD4.Signal=GPIO_Input
PD7.GPIOParameters=GPIO_PuPd,GPIO_Label
PD7.GPIO_Label=DIGI_IN_1
PD7.GPIO_PuPd=GPIO_PULLDOWN
PD7.Signal=GPIO_Input
PH0-OSC_IN.Mode=HSE-External-Clock-Source
PH0-OSC_IN.Signal=RCC_OSC_IN
PH1-OSC_OUT.Signal=GPIO_Input
RCC.HSE_VALUE=25000000
RCC.SYSCLKFreq_VALUE=550000000
RCC.SYSCLKSource=RCC_SYSCLKSOURCE_PLLCLK
board=custom
